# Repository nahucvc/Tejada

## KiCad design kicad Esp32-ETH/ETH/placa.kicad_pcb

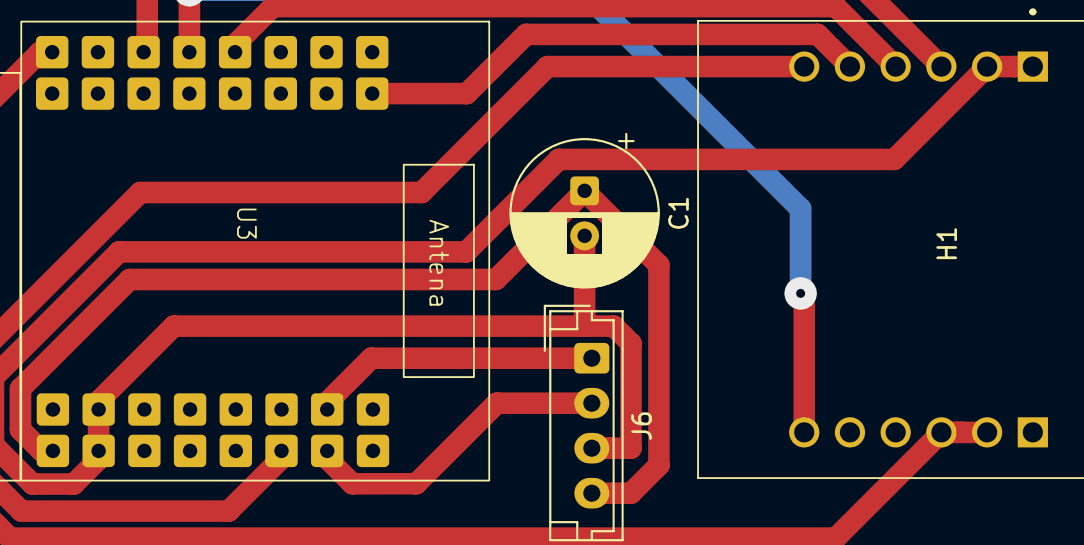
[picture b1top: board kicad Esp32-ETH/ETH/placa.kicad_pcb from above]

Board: 2 copper layers, 4 parts (0 on the bottom side), 10 nets.

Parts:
C1: 10uF; CP_Radial_D8.0mm_P2.50mm
H1: WIZ850IO
J6: ESP32; JST_EH_B4B-EH-A_1x04_P2.50mm_Vertical
U3: ESP32_loli

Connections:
5V: C1.1, J6.4, U3.103 (VBUS)
CS: H1.5 (SCNN), U3.1
GND: C1.2, H1.1 (GND_1), H1.2 (GND_2), J6.3, U3.100 (GND), U3.101 (GND)
INT: H1.6 (INTN), U3.35
MISO: H1.12 (MISO), U3.9
MOSI: H1.3 (MOSI), U3.11
RX: J6.2, U3.37
SCLK: H1.4 (SCLK), U3.7
TX: J6.1, U3.38
VCC: H1.8 (3.3V_1), H1.9 (3.3V_2), U3.105 (3.3v)

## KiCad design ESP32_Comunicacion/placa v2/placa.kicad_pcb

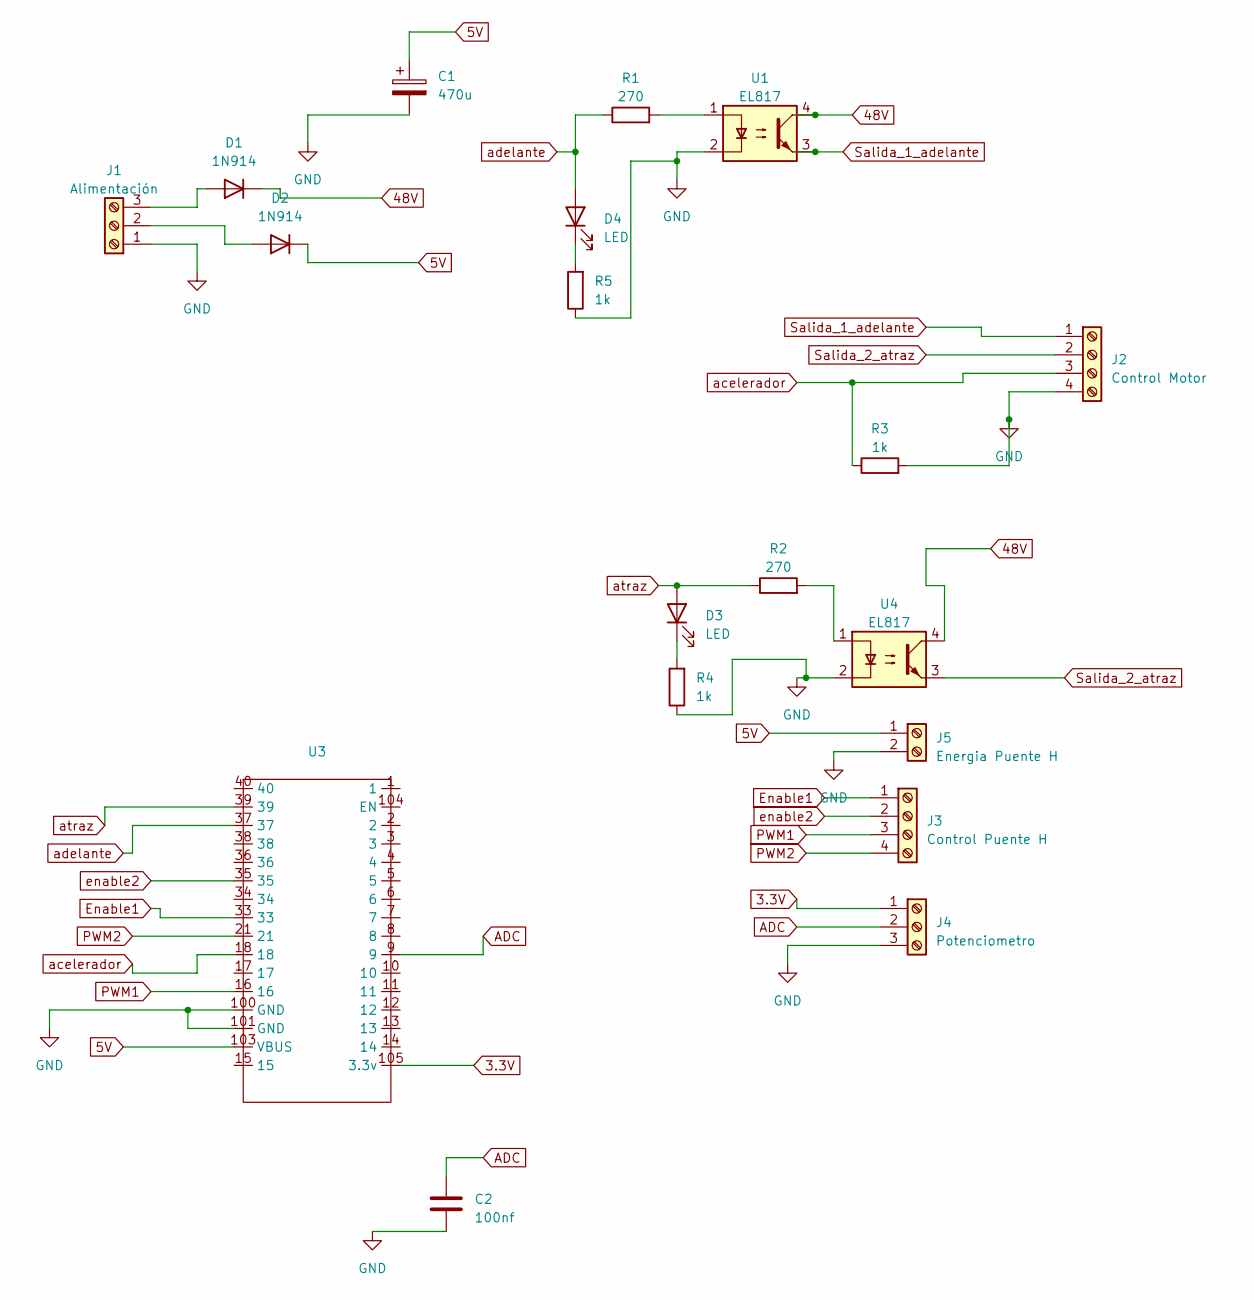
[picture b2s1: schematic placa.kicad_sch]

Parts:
C1: 470u; CP_Radial_D7.5mm_P2.50mm
C2: 100nf; C_Axial_L3.8mm_D2.6mm_P10.00mm_Horizontal
D1, D2: 1N914; D_DO-35_SOD27_P7.62mm_Horizontal
D3, D4: LED; D_0603_1608Metric
J1: Alimentación; TerminalBlock_Altech_AK300-3_P5.00mm
J2: Control Motor; TerminalBlock_Altech_AK300-4_P5.00mm
J3: Control Puente H; TerminalBlock_Altech_AK300-4_P5.00mm
J4: Potenciometro; TerminalBlock_Altech_AK300-3_P5.00mm
J5: Energia Puente H; TerminalBlock_Altech_AK300-2_P5.00mm
R1, R2: 270; R_0603_1608Metric
R3, R4, R5: 1k; R_0603_1608Metric
U1, U4: EL817; DIP-4_W7.62mm
U3: ESP32_loli

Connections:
3.3V: J4.1, U3.105 (3.3v)
5V: C1.1, D2.1 (K), J5.1, U3.103 (VBUS)
48V: D1.1 (K), U1.4, U4.4
ADC: C2.1, J4.2, U3.9
Enable1: J3.1, U3.33
GND: C1.2, C2.2, J1.1, J2.4, J4.3, J5.2, R3.2, R4.1, R5.1, U1.2, U3.100 (GND), U3.101 (GND), U4.2
unnamed: D1.2 (A), J1.3
unnamed: D2.2 (A), J1.2
unnamed: D3.1 (K), R4.2
unnamed: D4.1 (K), R5.2
unnamed: R1.2, U1.1
unnamed: R2.2, U4.1
PWM1: J3.3, U3.16
PWM2: J3.4, U3.21
Salida_1_adelante: J2.1, U1.3
Salida_2_atraz: J2.2, U4.3
acelerador: J2.3, R3.1, U3.18
adelante: D4.2 (A), R1.1, U3.37
atraz: D3.2 (A), R2.1, U3.39
enable2: J3.2, U3.35

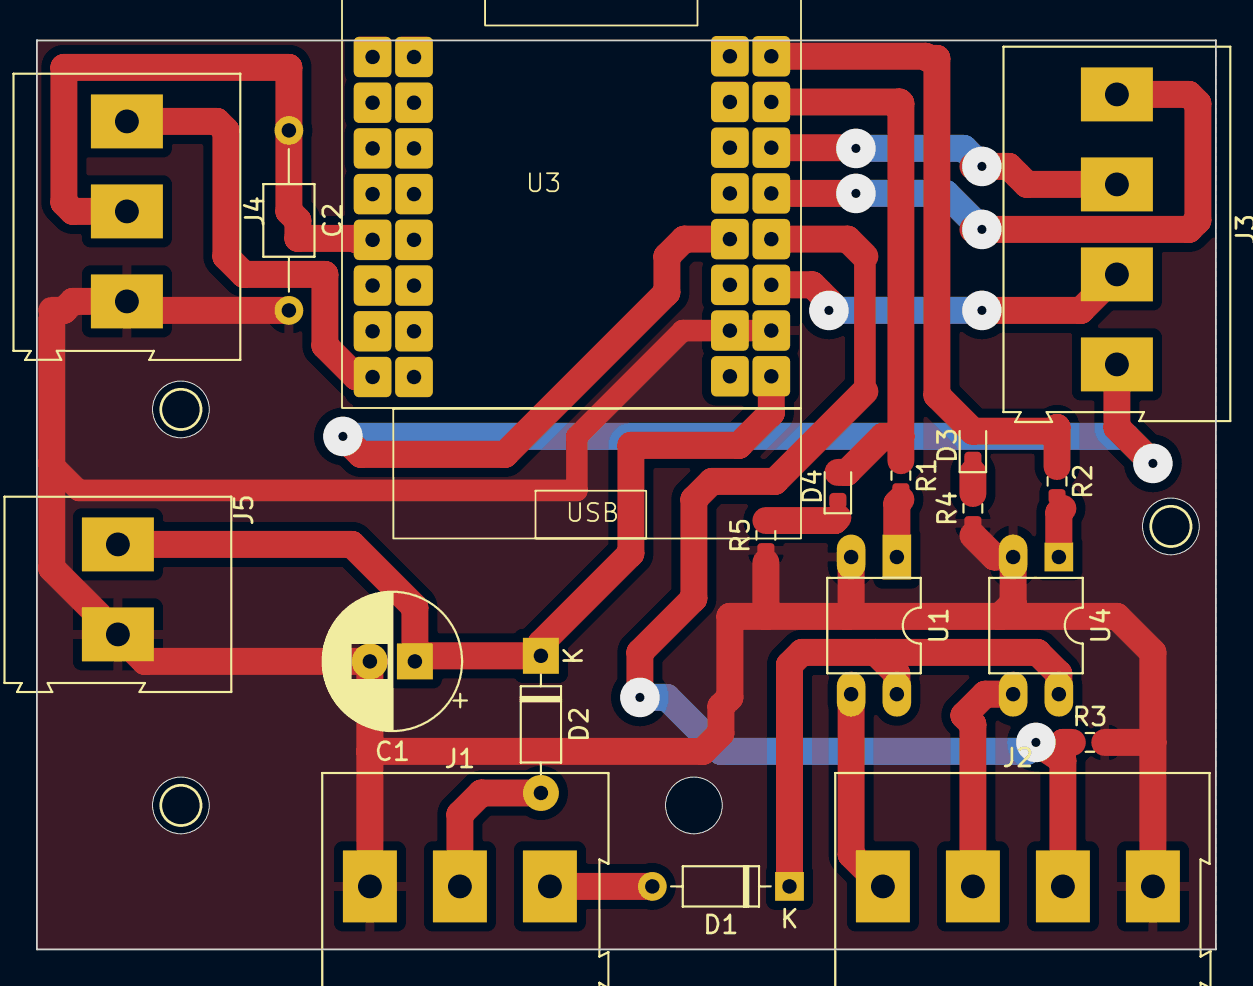
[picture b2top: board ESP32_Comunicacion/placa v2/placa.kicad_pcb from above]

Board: 2 copper layers, 65.5 x 50.5 mm, 19 parts (0 on the bottom side), 20 nets.

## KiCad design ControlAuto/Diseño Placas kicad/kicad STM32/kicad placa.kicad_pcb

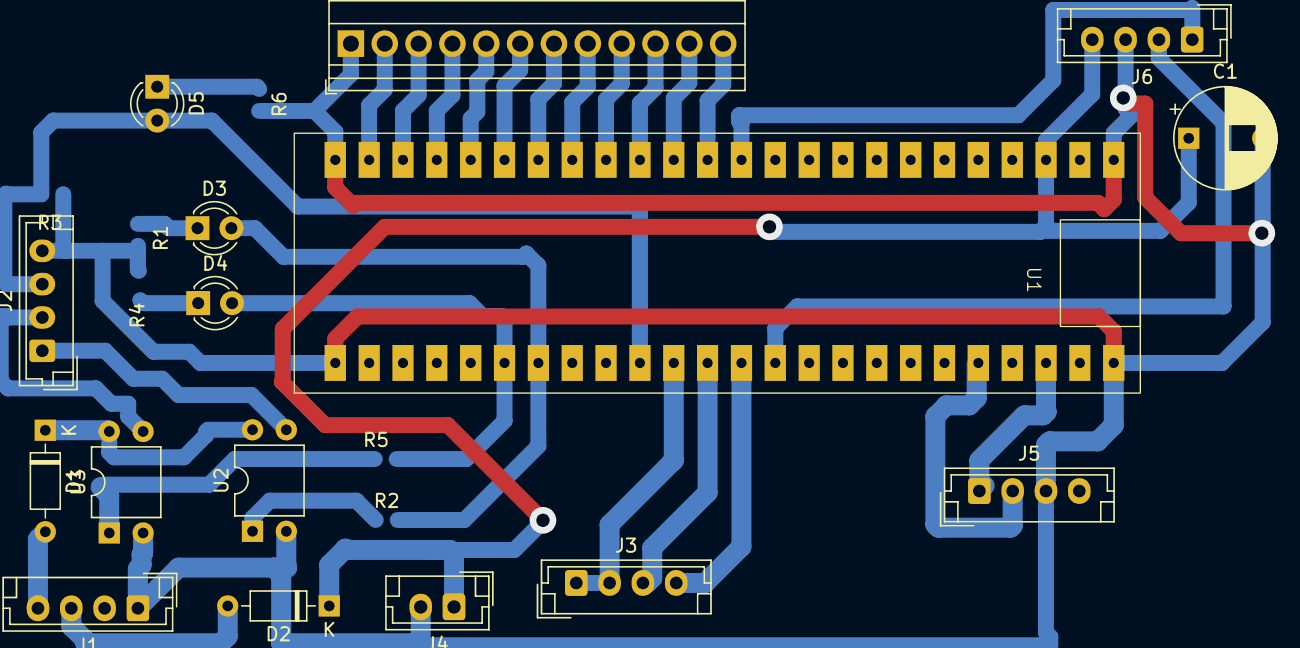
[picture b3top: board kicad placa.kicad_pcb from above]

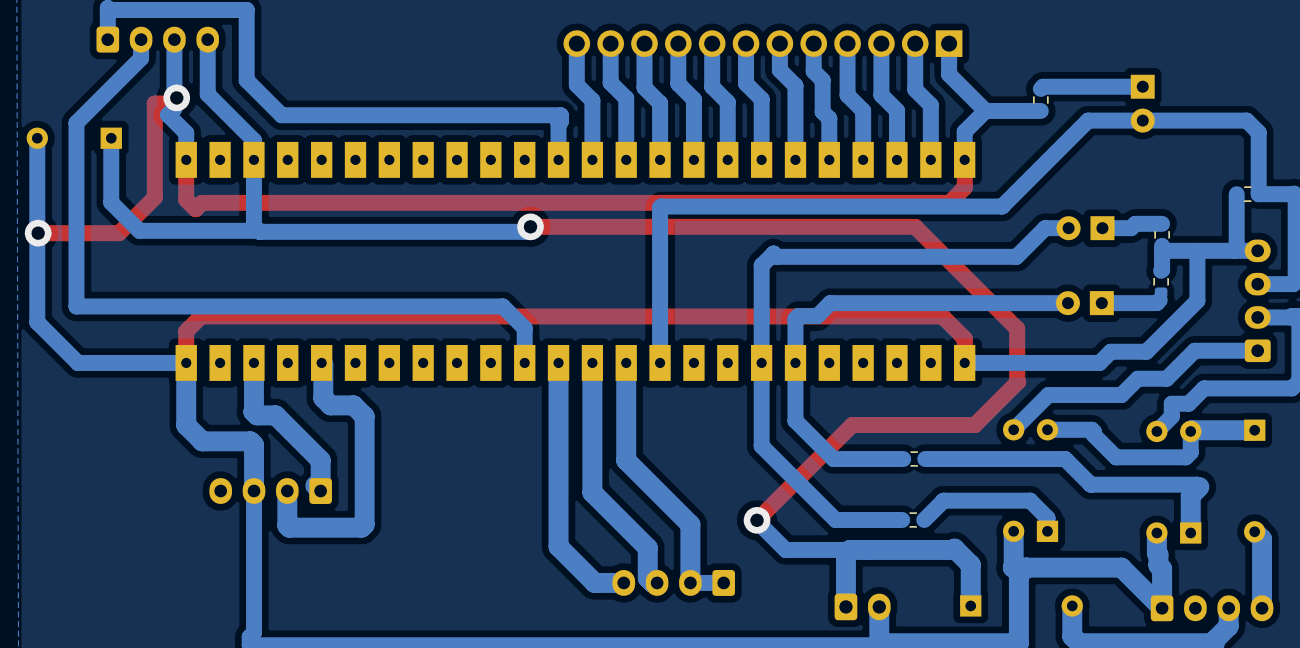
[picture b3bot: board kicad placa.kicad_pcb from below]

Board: 2 copper layers, 22 parts (6 on the bottom side), 33 nets.

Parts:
C1: 470u; CP_Radial_D7.5mm_P2.50mm
D1, D2: 1N914; D_DO-35_SOD27_P7.62mm_Horizontal
D3, D4, D5: LED; LED_D3.0mm
J1: Fuente; JST_EH_B4B-EH-A_1x04_P2.50mm_Vertical
J2: Control Motor; JST_EH_B4B-EH-A_1x04_P2.50mm_Vertical
J3: Control Puente H; JST_EH_B4B-EH-A_1x04_P2.50mm_Vertical
J4: Energia Puente H; JST_EH_B2B-EH-A_1x02_P2.50mm_Vertical
J5: Potenciometro; JST_EH_B4B-EH-A_1x04_P2.50mm_Vertical
J6: ESP32; JST_EH_B4B-EH-A_1x04_P2.50mm_Vertical
J7: Screw_Terminal_01x12; TerminalBlock_Xinya_XY308-2.54-12P_1x12_P2.54mm_Horizontal
R1, R3, R4, R6: 1k; R_0603_1608Metric
R2, R5: 270; R_0603_1608Metric
U1: STM32G431
U2, U3: EL817; DIP-4_W7.62mm

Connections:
3.3V: J5.1, U1.46 (3V3)
5V: C1.1, D2.1 (K), J4.1, J6.4, U1.3 (5V)
48V: D1.1 (K), U2.4, U3.4
ADC: J5.2, U1.44 (B11)
Enable1: J3.1, J3.2, U1.35 (A5)
GND: C1.2, J1.1, J2.4, J4.2, J5.3, J6.3, J7.1, R1.1, R3.2, R4.1, R6.1, U1.1 (G), U1.24 (G), U1.25 (G), U1.48 (G), U2.2, U3.2
unnamed: D1.2 (A), J1.4
unnamed: D2.2 (A), J1.3
unnamed: D3.1 (K), R1.2
unnamed: D4.1 (K), R4.2
unnamed: D5.1 (K), R6.2
unnamed: J7.2, U1.23 (B9)
unnamed: J7.3, U1.22 (B7)
unnamed: J7.4, U1.21 (B6)
unnamed: J7.5, U1.20 (B5)
unnamed: J7.6, U1.19 (B4)
unnamed: J7.7, U1.18 (B3)
unnamed: J7.8, U1.17 (C11)
unnamed: J7.9, U1.16 (C10)
unnamed: J7.10, U1.15 (A15)
unnamed: J7.11, U1.14 (A12)
unnamed: J7.12, U1.13 (A11)
unnamed: R2.2, U2.1
unnamed: R5.2, U3.1
PWM1: J3.3, U1.36 (A6)
PWM2: J3.4, U1.37 (A7)
RX: J6.1, U1.12 (A10)
Salida_1_adelante: J2.1, U2.3
Salida_2_atraz: J2.2, U3.3
TX: J6.2, U1.38 (C4)
acelerador: D5.2 (A), J2.3, R3.1, U1.34 (A4)
adelante: D3.2 (A), R2.1, U1.31 (A1)
atraz: D4.2 (A), R5.1, U1.30 (A0)

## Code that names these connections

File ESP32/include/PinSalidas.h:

#ifndef PINSALIDA_H
#define PINSALIDA_H


#ifdef LOLI 
#define ADCpin 9
#define PWMDeracha 16
#define PwmIzquierda 21
#define EnableDerecha 33 //enable1
#define EnableIzquierda 35 //enable 2
#define AnguloMaximo 50
#define Ganacia 2
#define _Adelante 37
#define _Atraz 39
#define _Acelerar 18
#endif

#ifdef WOROOM
#define ADCpin 34
#define PWMDeracha 32
#define PwmIzquierda 33
#define EnableDerecha 23
#define EnableIzquierda 22
#define AnguloMaximo 50
#define Ganacia 2
#define _Adelante 21
#define _Atraz 19
#define _Acelerar 25
#endif

// lectura maxima a la izquierda 1900
// lectura maxima a la derecha 3100
// medio 2585 

#endif

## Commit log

2025-04-12 Inicio
2025-04-12 Prueba 1
2025-04-23 Grafico ADC
2025-04-26 se agrego carpetas de proyectos anteriores
2025-04-26 mas agregados
2025-04-26 Cambio de placa
2025-04-28 Prueba 28/04/25
2025-04-28 Prueba2 28/04/25
2025-09-03 se paso a arduino
2025-09-03 se paso a arduino v2
2025-09-04 se agrego contenedor
2025-09-05 contenedor mejorado
2025-09-14 Se inicia una rama diferente para adelantar el proyecto
2025-09-15 Mejora del filtro y comunicación
2025-09-15 Mejora En la Recepcion
2025-09-15 Mejora del filtro
2025-09-18 Falta Calibrar ADC
2025-09-19 mejora serial v1
2025-09-19 Prueba Serial
2025-09-21 Comunicación Serial, Sin errores entre micros
2025-09-21 Con ETH
2025-09-25 Se modifico ETH
2025-10-07 Comunicacion con errores
2025-10-11 Se paso el Proyecto a STMCUBE
2025-10-12 Se añadio kicad de la placa ETH-ESP32
2025-10-12 ETH V
2025-10-12 Listo para Probar
2025-11-14 Prueba 2
2025-12-23 Restructuración del Repositorio
2025-12-26 Telemetria por teleplot funcionando
2026-01-08 Telemetria por teleplot funcionando v2
2026-01-10 Telemetria por teleplot funcionando v3
2026-05-26 Prueba ETH
